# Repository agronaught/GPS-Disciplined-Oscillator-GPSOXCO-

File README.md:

GPS-Disciplined-Oscillator-GPSOXCO-
===================================

Boards for my gps disciplined oscillator.

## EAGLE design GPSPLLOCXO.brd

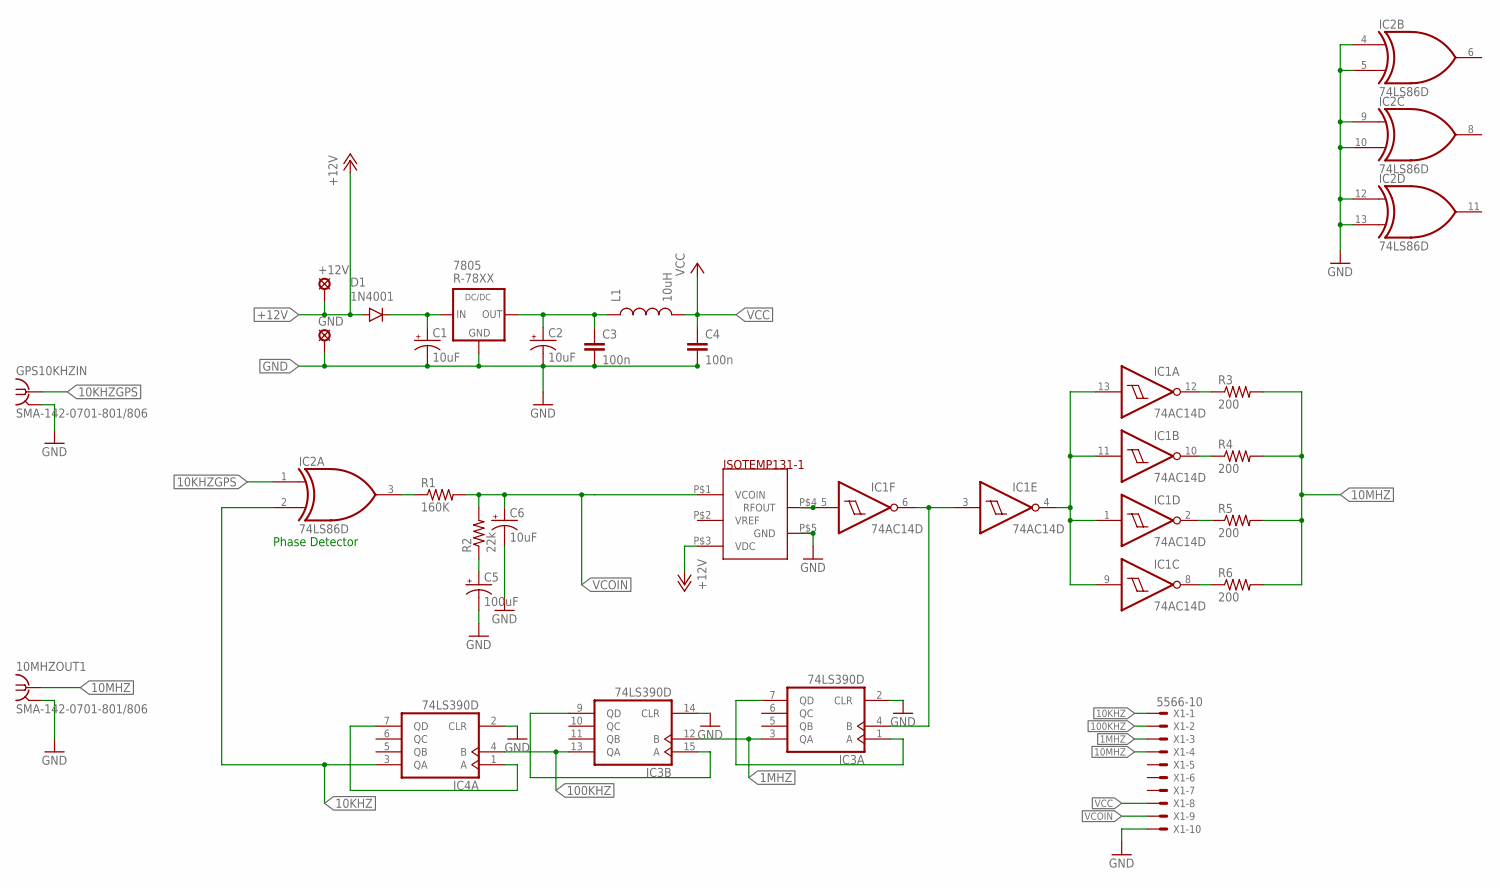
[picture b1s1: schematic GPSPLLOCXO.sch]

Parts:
10MHZOUT1: SMA-142-0701-801/806; J502-ND-142-0701-801/806
7805: R-78XX
+12V: LSP13
C1, C2, C6: 10uF; EIA3216
C3, C4: 100n; 0805
C5: 100uF; EIA7343
D1: 1N4001; SMA-DIODE
GND: LSP13
GPS10KHZIN: SMA-142-0701-801/806; J502-ND-142-0701-801/806
IC1: 74AC14D; SO14
IC2: 74LS86D; SO14
IC3, IC4: 74LS390D; SO16
ISOTEMP131-1: ISOTEMP-131-191; 131
L1: 10uH; 1210
R1: 160K; 0805
R2: 22k; 0805
R3, R4, R5, R6: 200; 0805
X1: 5566-10

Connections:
1MHZ: IC3.3 (QA), IC3.12 (B), X1.3
10KHZ: IC2.2 (I1), IC4.3 (QA), X1.1
10KHZGPS: GPS10KHZIN.1, IC2.1 (I0)
10MHZ: 10MHZOUT1.1, R3.2, R4.2, R5.2, R6.2, X1.4
100KHZ: IC3.13 (QA), IC4.4 (B), X1.2
+12V: +12V.MP, D1.A, ISOTEMP131-1.P$3 (VDC)
GND: 10MHZOUT1.G@1 (2), 10MHZOUT1.G@2 (2), 10MHZOUT1.G@3 (2), 10MHZOUT1.G@4 (2), 7805.2 (GND), C1.C (-), C2.C (-), C3.2, C4.2, C5.C (-), C6.C (-), GND.MP, GPS10KHZIN.G@1 (2), GPS10KHZIN.G@2 (2), GPS10KHZIN.G@3 (2), GPS10KHZIN.G@4 (2), IC1.7 (GND), IC2.4 (I0), IC2.5 (I1), IC2.7 (GND), IC2.9 (I0), IC2.10 (I1), IC2.12 (I0), IC2.13 (I1), IC3.2 (CLR), IC3.8 (GND), IC3.14 (CLR), IC4.2 (CLR), IC4.8 (GND), ISOTEMP131-1.P$5 (GND), X1.10
unnamed: 7805.1 (IN), C1.A (+), D1.C
unnamed: IC2.3 (O), R1.1
unnamed: C5.A (+), R2.1
unnamed: IC1.5 (I), ISOTEMP131-1.P$4 (RFOUT)
unnamed: IC1.3 (I), IC1.6 (O), IC3.4 (B)
unnamed: IC3.1 (A), IC3.7 (QD)
unnamed: IC3.9 (QD), IC3.15 (A)
unnamed: IC4.1 (A), IC4.7 (QD)
unnamed: IC1.1 (I), IC1.4 (O), IC1.9 (I), IC1.11 (I), IC1.13 (I)
unnamed: IC1.8 (O), R6.1
unnamed: IC1.2 (O), R5.1
unnamed: IC1.10 (O), R4.1
unnamed: IC1.12 (O), R3.1
VCC: C4.1, IC1.14 (VCC), IC2.14 (VCC), IC3.16 (VCC), IC4.16 (VCC), L1.2, X1.8
VCC-5V: 7805.3 (OUT), C2.A (+), C3.1, L1.1
VCOIN: C6.A (+), ISOTEMP131-1.P$1 (VCOIN), R1.2, R2.2, X1.9

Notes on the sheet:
Phase Detector

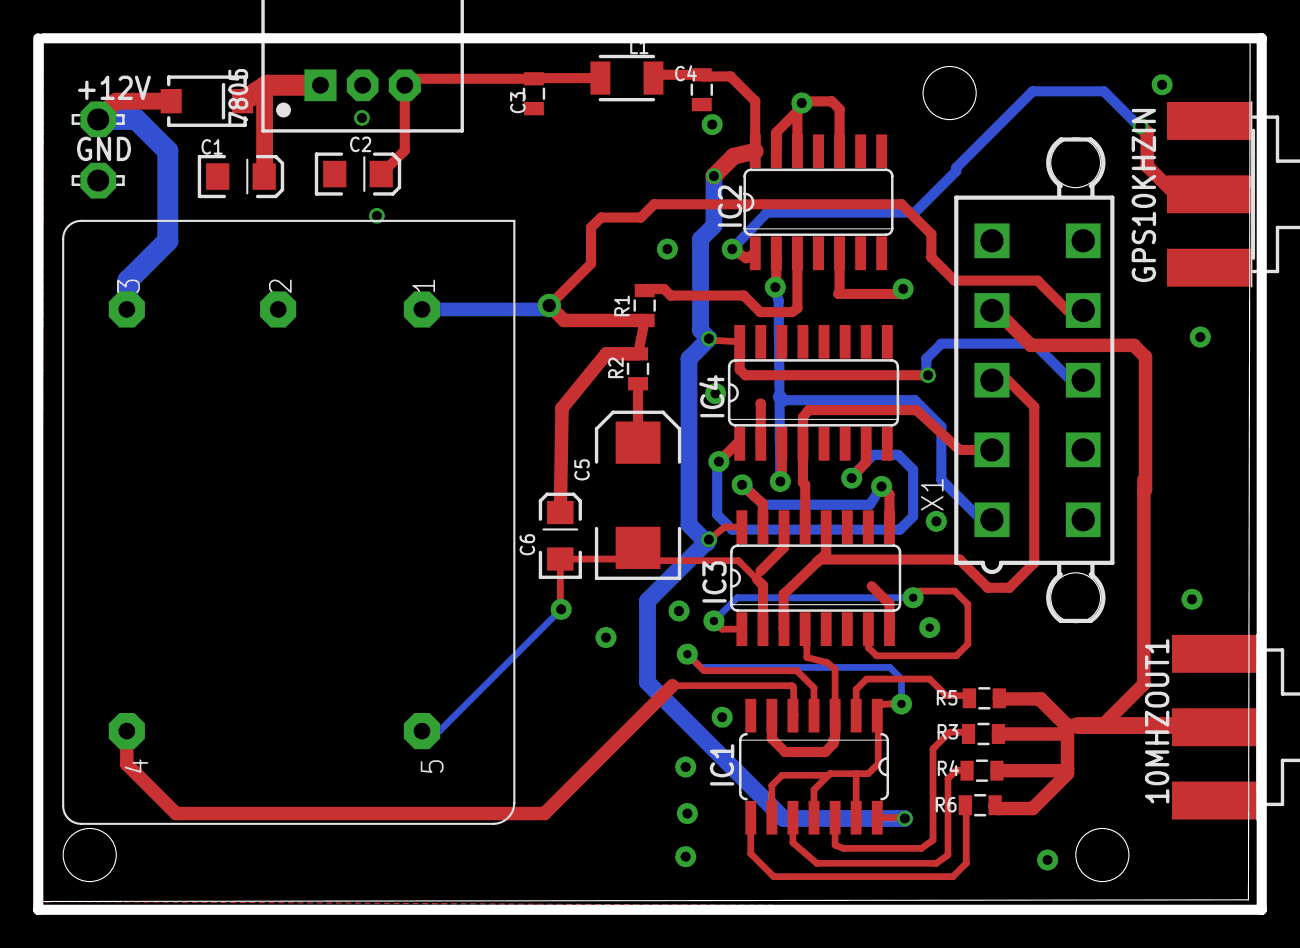
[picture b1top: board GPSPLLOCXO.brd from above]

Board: 2 copper layers, 73.7 x 52.5 mm, 25 parts (0 on the bottom side), 23 nets.

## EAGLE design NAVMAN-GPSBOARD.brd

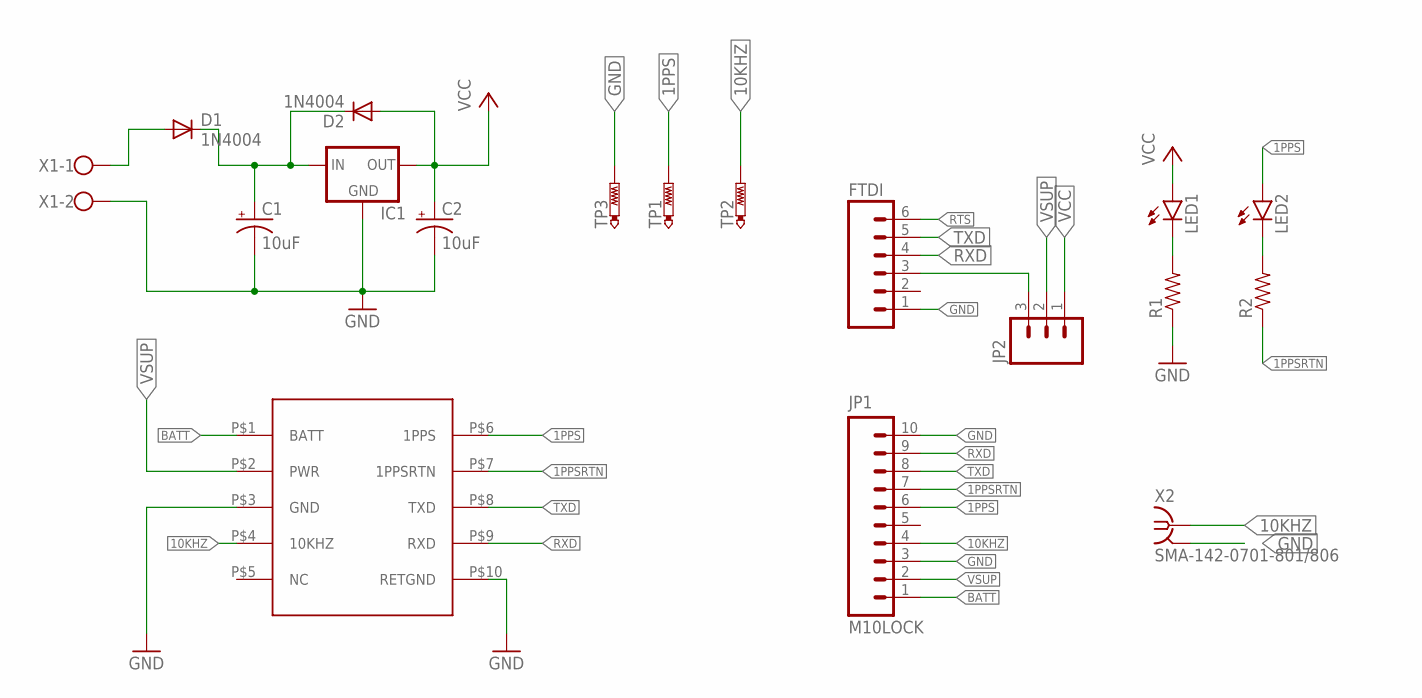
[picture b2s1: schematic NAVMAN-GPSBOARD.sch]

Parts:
C1, C2: 10uF; CPOL-RADIAL-10UF-25V
D1, D2: 1N4004; DO41-10
FTDI: M06LOCK; 1X06_LOCK
IC1: V_REG_78XXSINK; TO220-IGO
JP1: M10LOCK; 1X10_LOCK
JP2: M03LOCK; 1X03_LOCK
LED1, LED2: LED5MM
R1, R2: RESISTORPTH-1/4W; AXIAL-0.4
TP1, TP2, TP3: PTR1PAD1-20Y; P1-20Y
TU60-D001: NAVMANJUPITERTU60; TU60-D001
X1: W237-102
X2: SMA-142-0701-801/806; J502-ND-142-0701-801/806

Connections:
1PPS: JP1.6, LED2.A, TP1.TP, TU60-D001.P$6 (1PPS)
1PPSRTN: JP1.7, R2.P$1 (1), TU60-D001.P$7 (1PPSRTN)
10KHZ: JP1.4, TP2.TP, TU60-D001.P$4 (10KHZ), X2.1
BATT: JP1.1, TU60-D001.P$1 (BATT)
GND: C1.2 (-), C2.2 (-), FTDI.1, IC1.GND, JP1.3, JP1.10, R1.P$1 (1), TP3.TP, TU60-D001.P$3 (GND), TU60-D001.P$10 (RETGND), X1.2, X2.G@1 (2), X2.G@2 (2), X2.G@3 (2), X2.G@4 (2)
unnamed: C1.1 (+), D1.C, D2.C, IC1.IN
unnamed: LED1.K (C), R1.P$2 (2)
unnamed: LED2.K (C), R2.P$2 (2)
unnamed: FTDI.3, JP2.3
unnamed: D1.A, X1.1
RTS: FTDI.6
RXD: FTDI.4, JP1.9, TU60-D001.P$9 (RXD)
TXD: FTDI.5, JP1.8, TU60-D001.P$8 (TXD)
VCC: C2.1 (+), D2.A, IC1.OUT, JP2.1, LED1.A
VSUP: JP1.2, JP2.2, TU60-D001.P$2 (PWR)

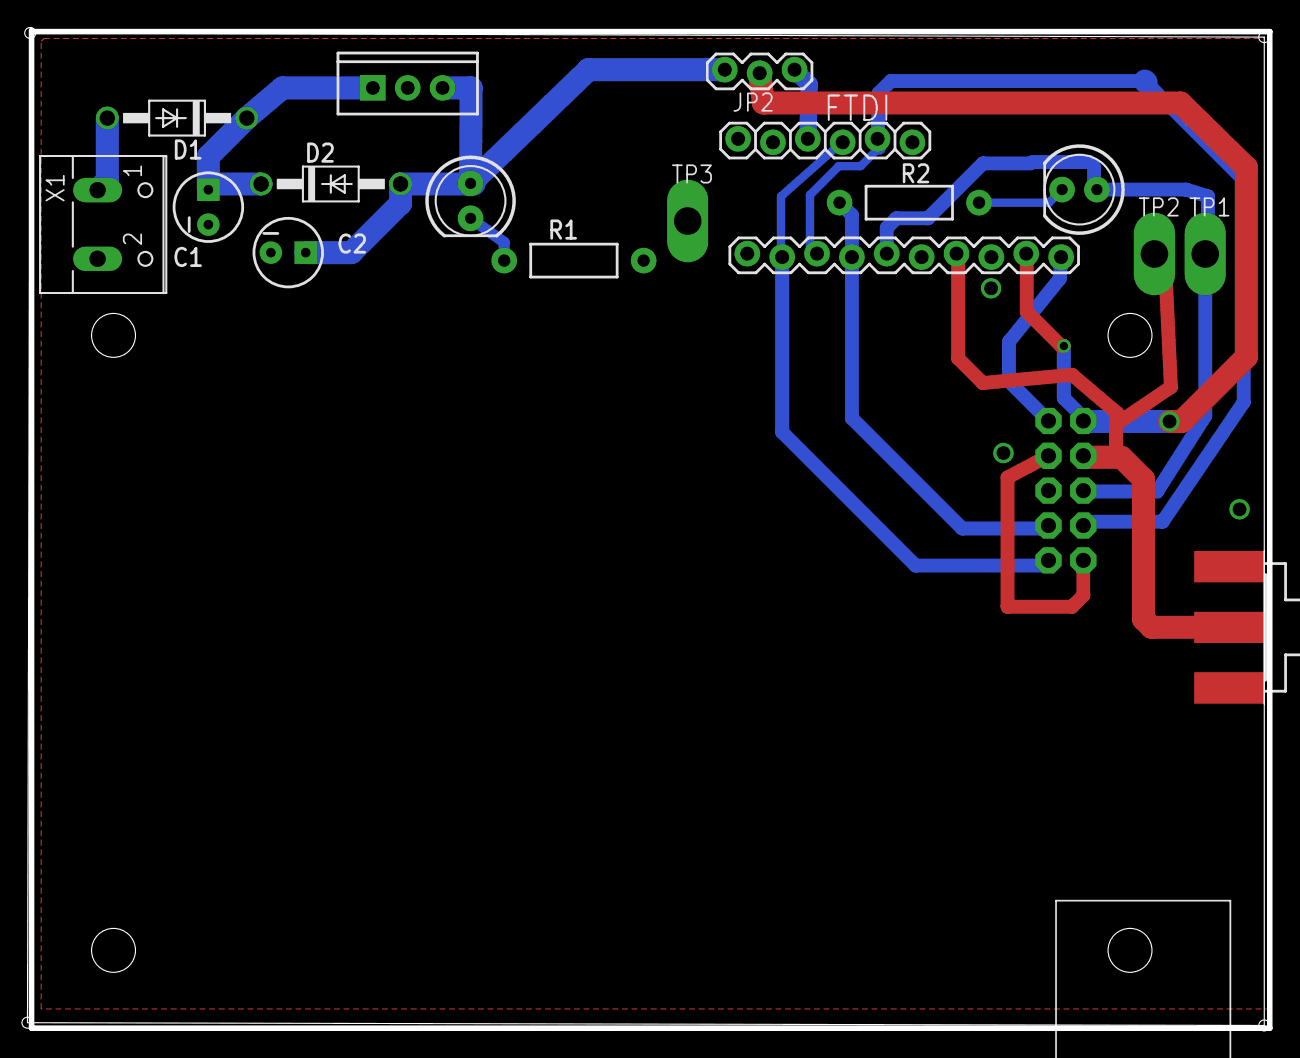
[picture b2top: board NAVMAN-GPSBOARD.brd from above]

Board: 2 copper layers, 90.3 x 72.7 mm, 18 parts (0 on the bottom side), 14 nets.

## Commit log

2014-08-13 Added git repository to this version
2014-08-13 Modified board to suite CNC/Milling
2014-08-18 Corrected FTDI mapping, added header to select power source.
2014-08-19 Updated gps module design
2014-08-20 Updated... generated gerbers
2015-07-24 Fixed serious errors in power supply nets... should actually work now without blowing components.

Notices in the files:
parts and their libraries:
SparkFun-DiscreteSemi: Licensing: Creative Commons ShareAlike 4.0 International - https://creativecommons.org/licenses/by-sa/4.0
recom-intl: Copyright (C) 2010, Bob Starr
